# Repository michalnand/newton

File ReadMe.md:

# newton - outdoor robot

**first look from stereovision camera**

# hardware

- nvidia jetson nano 128Cuda cores
- two cameras, wifi
- sensored brushless motor, 160A ESC
- some random servo
- chassis : RC truggy 1:10 scale
- power 2S LiPol

TODO :
- pwm and gyro board

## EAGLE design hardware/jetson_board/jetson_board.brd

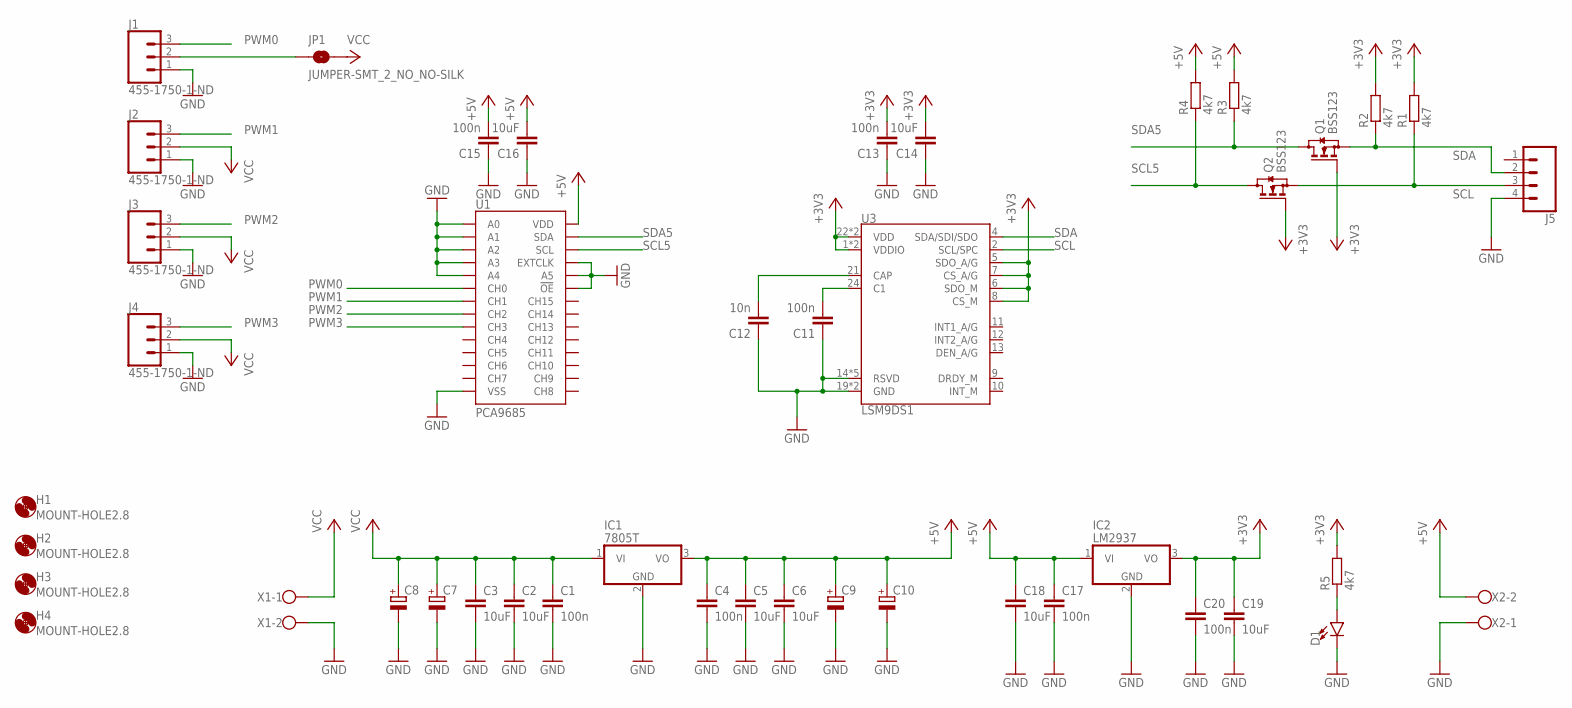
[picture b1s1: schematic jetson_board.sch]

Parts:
C1, C4, C11, C13, C15, C17, C20: 100n; C0805
C2, C3, C5, C6, C14, C16, C18, C19: 10uF; C0805
C7, C8, C9, C10: CPOL-EUUD-8X10; UD-8X10_NICHICON
C12: 10n; C0805
D1: LED1206; LED-1206
H1, H2, H3, H4: MOUNT-HOLE2.8; 2,8
IC1: 7805T; TO220H
IC2: LM2937; TO263-3
J1, J2, J3, J4: 455-1750-1-ND; 1X03
J5: CONN_04LONGPADS; 1X04_LONGPADS
JP1: JUMPER-SMT_2_NO_NO-SILK; SMT-JUMPER_2_NO_NO-SILK
Q1, Q2: BSS123; SOT23
R1, R2, R3, R4, R5: 4k7; R0805
U1: PCA9685; TSSOP-28_4MM
U3: LSM9DS1; LGA-24-3.5X3
X1, X2: W237-102

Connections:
+3V3: C13.2, C14.2, C19.1, C20.1, IC2.3 (VO), Q1.1 (G), Q2.1 (G), R1.2, R2.2, R5.2, U3.1 (VDDIO), U3.3 (VDDIO), U3.5 (SDO_A/G), U3.6 (SDO_M), U3.7 (CS_A/G), U3.8 (CS_M), U3.22 (VDD), U3.23 (VDD)
+5V: C4.1, C5.1, C6.1, C9.+, C10.+, C15.2, C16.2, C17.1, C18.1, IC1.3 (VO), IC2.1 (VI), R3.2, R4.2, U1.28 (VDD), X2.2
GND: C1.2, C2.2, C3.2, C4.2, C5.2, C6.2, C7.-, C8.-, C9.-, C10.-, C11.1, C12.1, C13.1, C14.1, C15.1, C16.1, C17.2, C18.2, C19.2, C20.2, D1.C, IC1.2 (GND), IC2.2 (GND), J1.1, J2.1, J3.1, J4.1, J5.4, U1.1 (A0), U1.2 (A1), U1.3 (A2), U1.4 (A3), U1.5 (A4), U1.14 (VSS), U1.23 (!OE), U1.24 (A5), U1.25 (EXTCLK), U3.14 (RSVD), U3.15 (RSVD), U3.16 (RSVD), U3.17 (RSVD), U3.18 (RSVD), U3.19 (GND), U3.20 (GND), X1.2, X2.1
unnamed: J1.2, JP1.1
unnamed: C11.2, U3.24 (C1)
unnamed: C12.2, U3.21 (CAP)
unnamed: D1.A, R5.1
PWM0: J1.3, U1.6 (CH0)
PWM1: J2.3, U1.7 (CH1)
PWM2: J3.3, U1.8 (CH2)
PWM3: J4.3, U1.9 (CH3)
SCL: J5.3, Q2.2 (S), R1.1, U3.2 (SCL/SPC)
SCL5: Q2.3 (D), R4.1, U1.26 (SCL)
SDA: J5.2, Q1.2 (S), R2.1, U3.4 (SDA/SDI/SDO)
SDA5: Q1.3 (D), R3.1, U1.27 (SDA)
VCC: C1.1, C2.1, C3.1, C7.+, C8.+, IC1.1 (VI), J2.2, J3.2, J4.2, JP1.2, X1.1

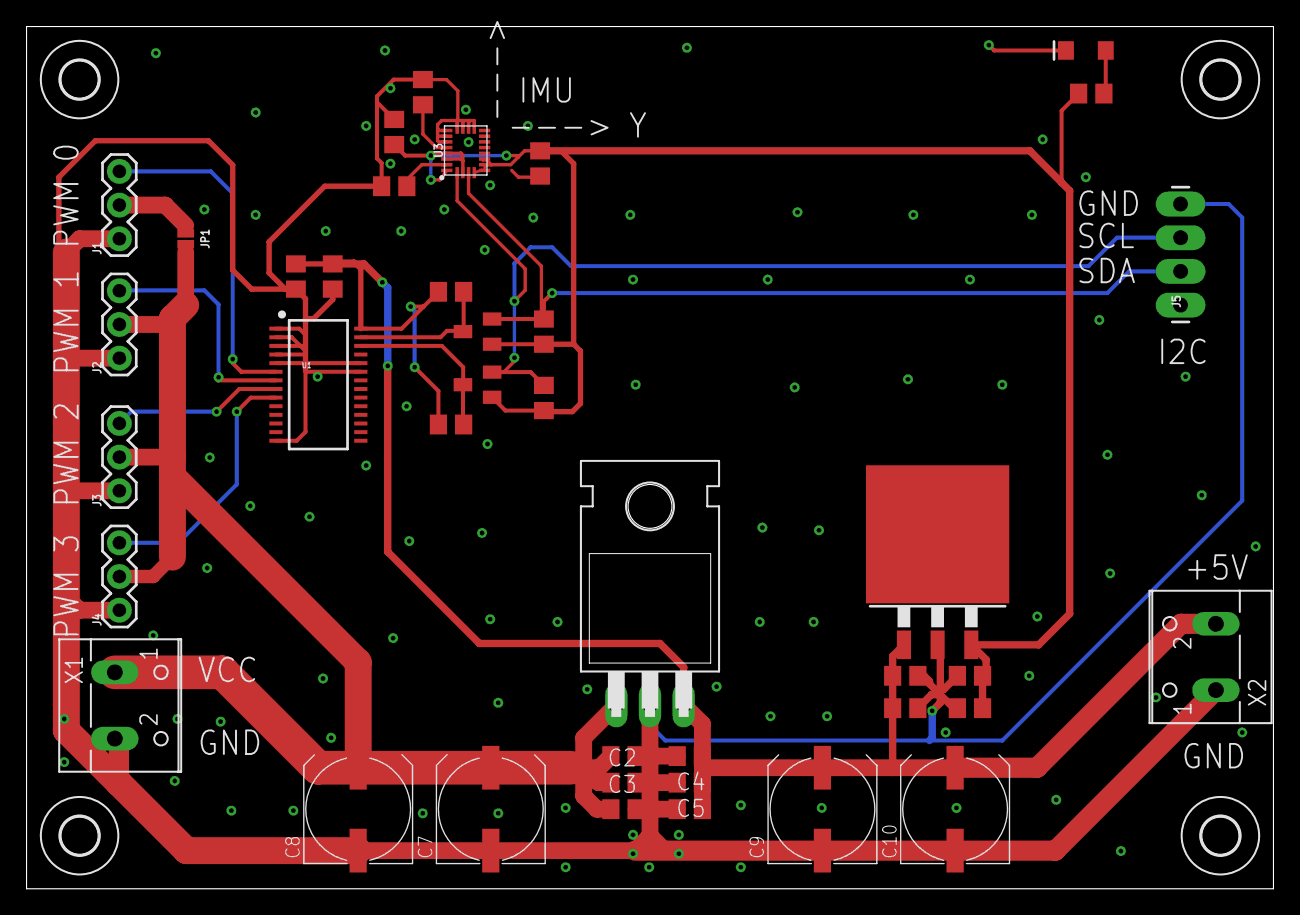
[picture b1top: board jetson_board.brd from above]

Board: 2 copper layers, 94.0 x 65.0 mm, 44 parts (0 on the bottom side), 16 nets.

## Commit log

2020-11-16 initial

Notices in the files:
parts and their libraries:
SparkFun-IC-Special-Function: Licensing: Creative Commons ShareAlike 4.0 International - https://creativecommons.org/licenses/by-sa/4.0
